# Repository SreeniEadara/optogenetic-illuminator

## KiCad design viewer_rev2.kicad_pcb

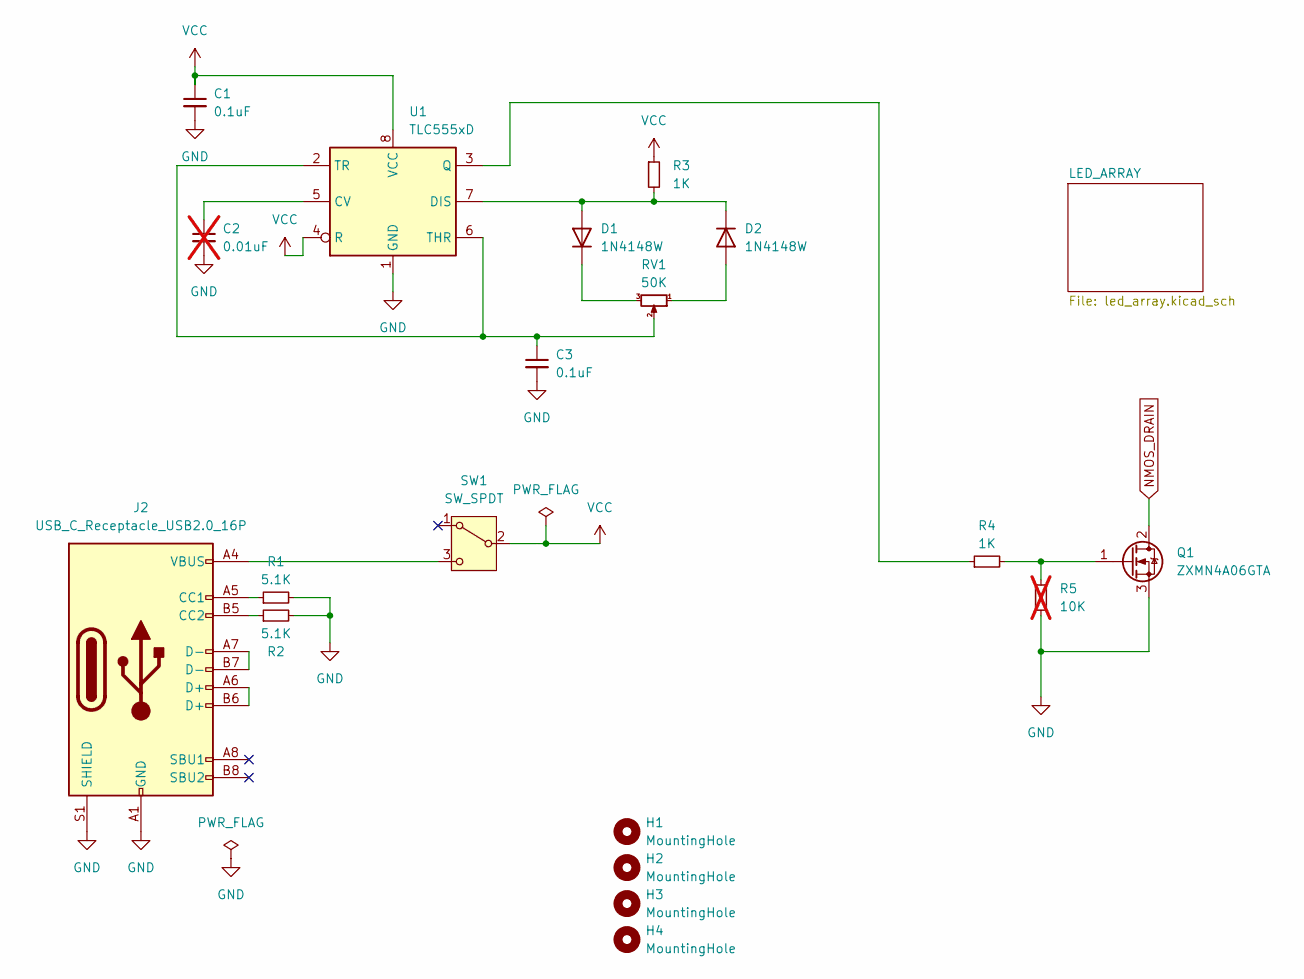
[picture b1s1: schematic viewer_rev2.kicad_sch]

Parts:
C1, C3: 0.1uF; C_0603_1608Metric; JLC C14663
C2: 0.01uF; C_0603_1608Metric; JLC C57112; not fitted
D1, D2: 1N4148W; D_SOD-123; DigiKey 1N4148W-E3-18CT-ND
H1, H2, H3, H4: MountingHole; MountingHole_3.2mm_M3_DIN965_Pad
J2: USB_C_Receptacle_USB2.0_16P; USB_C_Receptacle_GCT_USB4105-xx-A_16P_TopMnt_Horizontal; JLC C3039294
Q1: ZXMN4A06GTA; SOT-223-3_TabPin2; DigiKey ZXMN4A06GCT-ND
R1, R2: 5.1K; R_0603_1608Metric; JLC C23186
R3, R4: 1K; R_0603_1608Metric; JLC C21190
R5: 10K; R_0603_1608Metric; JLC C25804; not fitted
RV1: 50K; Potentiometer_Bourns_PTV09A-2_Single_Horizontal; DigiKey PTV09A-2020F-B503-ND
SW1: SW_SPDT; 1101MxSxAxx; DigiKey CKN11550-ND
U1: TLC555xD; SOIC-8_3.9x4.9mm_P1.27mm; DigiKey 296-1336-1-ND

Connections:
GND: C1.2, C2.2, C3.2, J2.A1 (GND), J2.A12 (GND), J2.B1 (GND), J2.B12 (GND), J2.S1 (SHIELD), Q1.3 (S), R1.2, R2.2, R5.2, U1.1 (GND)
NMOS_DRAIN: Q1.2 (D); also elsewhere on the board
unnamed: D1.2 (A), D2.1 (K), R3.2, U1.7 (DIS)
unnamed: D1.1 (K), RV1.3
unnamed: D2.2 (A), RV1.1
unnamed: J2.A5 (CC1), R1.1
unnamed: J2.B5 (CC2), R2.1
unnamed: J2.A6 (D+), J2.B6 (D+)
unnamed: J2.A7 (D-), J2.B7 (D-)
unnamed: Q1.1 (G), R4.2, R5.1
unnamed: J2.A4 (VBUS), J2.A9 (VBUS), J2.B4 (VBUS), J2.B9 (VBUS), SW1.3 (C)
unnamed: C2.1, U1.5 (CV)
unnamed: R4.1, U1.3 (Q)
unnamed: C3.1, RV1.2, U1.2 (TR), U1.6 (THR)
VCC: C1.1, R3.1, SW1.2 (B), U1.4 (R), U1.8 (VCC); also elsewhere on the board

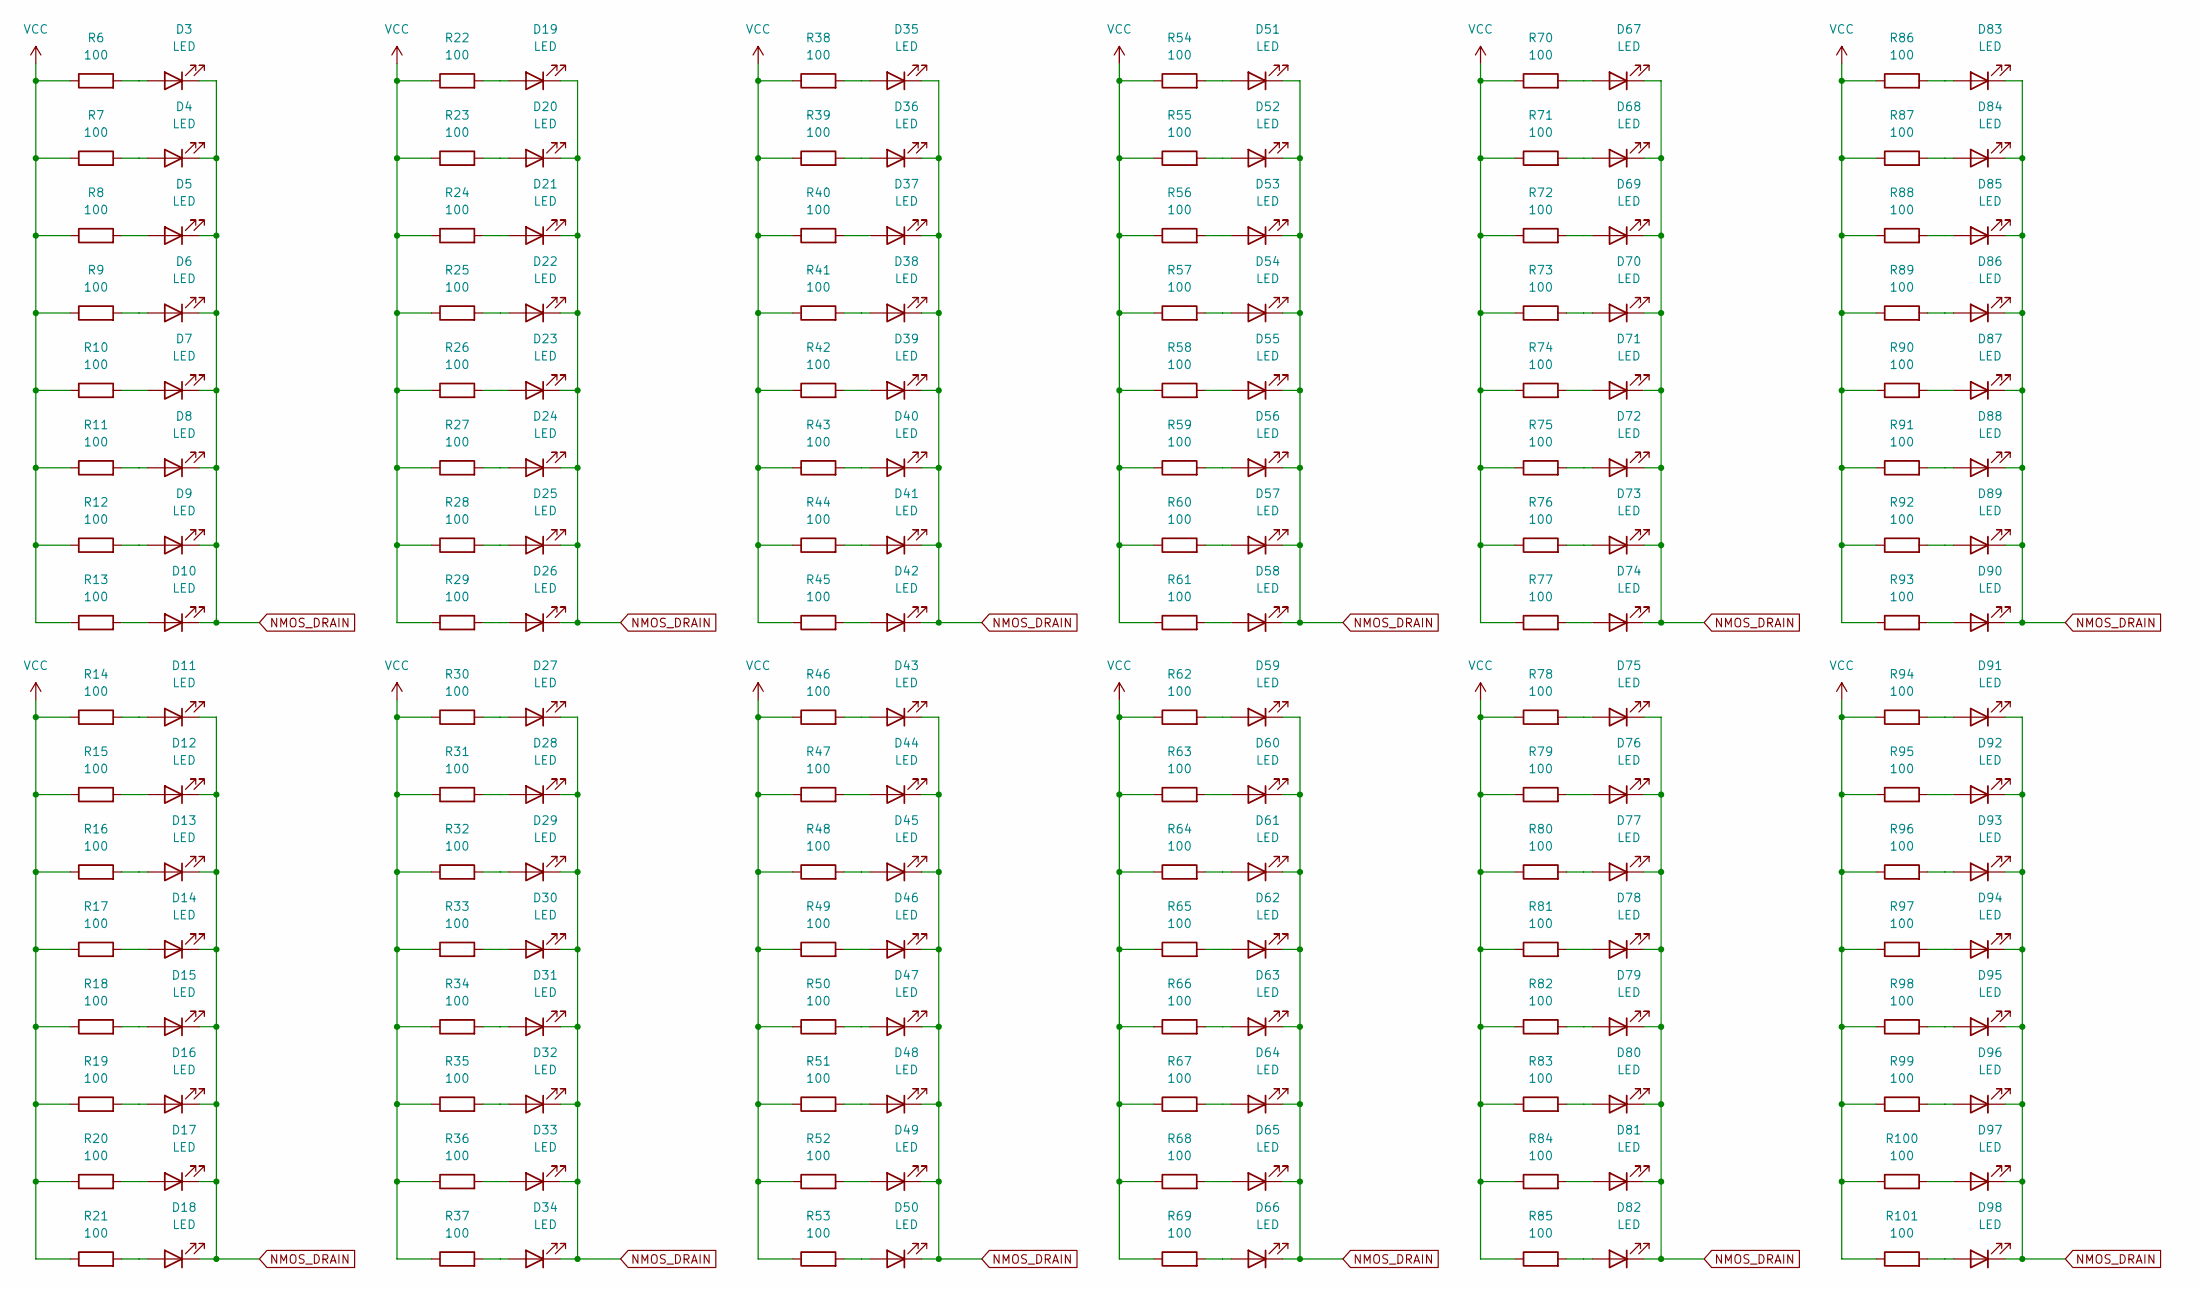
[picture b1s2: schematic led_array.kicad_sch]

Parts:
D3, D4, D5, D6, D7, D8, D9, D10, D11, D12, D13, D14, D15, D16, D17, D18, D19, D20, D21, D22, D23, D24, D25, D26, D27, D28, D29, D30, D31, D32, D33, D34, D35, D36, D37, D38, D39, D40, D41, D42, D43, D44, D45, D46, D47, D48, D49, D50, D51, D52, D53, D54, D55, D56, D57, D58, D59, D60, D61, D62, D63, D64, D65, D66, D67, D68, D69, D70, D71, D72, D73, D74, D75, D76, D77, D78, D79, D80, D81, D82, D83, D84, D85, D86, D87, D88, D89, D90, D91, D92, D93, D94, D95, D96, D97, D98: LED; LED_0603_1608Metric; DigiKey 754-1434-1-ND
R6, R7, R8, R9, R10, R11, R12, R13, R14, R15, R16, R17, R18, R19, R20, R21, R22, R23, R24, R25, R26, R27, R28, R29, R30, R31, R32, R33, R34, R35, R36, R37, R38, R39, R40, R41, R42, R43, R44, R45, R46, R47, R48, R49, R50, R51, R52, R53, R54, R55, R56, R57, R58, R59, R60, R61, R62, R63, R64, R65, R66, R67, R68, R69, R70, R71, R72, R73, R74, R75, R76, R77, R78, R79, R80, R81, R82, R83, R84, R85, R86, R87, R88, R89, R90, R91, R92, R93, R94, R95, R96, R97, R98, R99, R100, R101: 100; R_0603_1608Metric; JLC C22775

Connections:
NMOS_DRAIN: D3.1 (K), D4.1 (K), D5.1 (K), D6.1 (K), D7.1 (K), D8.1 (K), D9.1 (K), D10.1 (K), D11.1 (K), D12.1 (K), D13.1 (K), D14.1 (K), D15.1 (K), D16.1 (K), D17.1 (K), D18.1 (K), D19.1 (K), D20.1 (K), D21.1 (K), D22.1 (K), D23.1 (K), D24.1 (K), D25.1 (K), D26.1 (K), D27.1 (K), D28.1 (K), D29.1 (K), D30.1 (K), D31.1 (K), D32.1 (K), D33.1 (K), D34.1 (K), D35.1 (K), D36.1 (K), D37.1 (K), D38.1 (K), D39.1 (K), D40.1 (K), D41.1 (K), D42.1 (K), D43.1 (K), D44.1 (K), D45.1 (K), D46.1 (K), D47.1 (K), D48.1 (K), D49.1 (K), D50.1 (K), D51.1 (K), D52.1 (K), D53.1 (K), D54.1 (K), D55.1 (K), D56.1 (K), D57.1 (K), D58.1 (K), D59.1 (K), D60.1 (K), D61.1 (K), D62.1 (K), D63.1 (K), D64.1 (K), D65.1 (K), D66.1 (K), D67.1 (K), D68.1 (K), D69.1 (K), D70.1 (K), D71.1 (K), D72.1 (K), D73.1 (K), D74.1 (K), D75.1 (K), D76.1 (K), D77.1 (K), D78.1 (K), D79.1 (K), D80.1 (K), D81.1 (K), D82.1 (K), D83.1 (K), D84.1 (K), D85.1 (K), D86.1 (K), D87.1 (K), D88.1 (K), D89.1 (K), D90.1 (K), D91.1 (K), D92.1 (K), D93.1 (K), D94.1 (K), D95.1 (K), D96.1 (K), D97.1 (K), D98.1 (K); also elsewhere on the board
unnamed: D3.2 (A), R6.2
unnamed: D4.2 (A), R7.2
unnamed: D5.2 (A), R8.2
unnamed: D6.2 (A), R9.2
unnamed: D7.2 (A), R10.2
unnamed: D8.2 (A), R11.2
unnamed: D9.2 (A), R12.2
unnamed: D10.2 (A), R13.2
unnamed: D11.2 (A), R14.2
unnamed: D12.2 (A), R15.2
unnamed: D13.2 (A), R16.2
unnamed: D14.2 (A), R17.2
unnamed: D15.2 (A), R18.2
unnamed: D16.2 (A), R19.2
unnamed: D17.2 (A), R20.2
unnamed: D18.2 (A), R21.2
unnamed: D19.2 (A), R22.2
unnamed: D20.2 (A), R23.2
unnamed: D21.2 (A), R24.2
unnamed: D22.2 (A), R25.2
unnamed: D23.2 (A), R26.2
unnamed: D24.2 (A), R27.2
unnamed: D25.2 (A), R28.2
unnamed: D26.2 (A), R29.2
unnamed: D27.2 (A), R30.2
unnamed: D28.2 (A), R31.2
unnamed: D29.2 (A), R32.2
unnamed: D30.2 (A), R33.2
unnamed: D31.2 (A), R34.2
unnamed: D32.2 (A), R35.2
unnamed: D33.2 (A), R36.2
unnamed: D34.2 (A), R37.2
unnamed: D35.2 (A), R38.2
unnamed: D36.2 (A), R39.2
unnamed: D37.2 (A), R40.2
unnamed: D38.2 (A), R41.2
unnamed: D39.2 (A), R42.2
unnamed: D40.2 (A), R43.2
unnamed: D41.2 (A), R44.2
unnamed: D42.2 (A), R45.2
unnamed: D43.2 (A), R46.2
unnamed: D44.2 (A), R47.2
unnamed: D45.2 (A), R48.2
unnamed: D46.2 (A), R49.2
unnamed: D47.2 (A), R50.2
unnamed: D48.2 (A), R51.2
unnamed: D49.2 (A), R52.2
unnamed: D50.2 (A), R53.2
unnamed: D51.2 (A), R54.2
unnamed: D52.2 (A), R55.2
unnamed: D53.2 (A), R56.2
unnamed: D54.2 (A), R57.2
unnamed: D55.2 (A), R58.2
unnamed: D56.2 (A), R59.2
unnamed: D57.2 (A), R60.2
unnamed: D58.2 (A), R61.2
unnamed: D59.2 (A), R62.2
unnamed: D60.2 (A), R63.2
unnamed: D61.2 (A), R64.2
unnamed: D62.2 (A), R65.2
unnamed: D63.2 (A), R66.2
unnamed: D64.2 (A), R67.2
unnamed: D65.2 (A), R68.2
unnamed: D66.2 (A), R69.2
unnamed: D67.2 (A), R70.2
unnamed: D68.2 (A), R71.2
unnamed: D69.2 (A), R72.2
unnamed: D70.2 (A), R73.2
unnamed: D71.2 (A), R74.2
unnamed: D72.2 (A), R75.2
unnamed: D73.2 (A), R76.2
unnamed: D74.2 (A), R77.2
unnamed: D75.2 (A), R78.2
unnamed: D76.2 (A), R79.2
unnamed: D77.2 (A), R80.2
unnamed: D78.2 (A), R81.2
unnamed: D79.2 (A), R82.2
unnamed: D80.2 (A), R83.2
unnamed: D81.2 (A), R84.2
unnamed: D82.2 (A), R85.2
unnamed: D83.2 (A), R86.2
unnamed: D84.2 (A), R87.2
unnamed: D85.2 (A), R88.2
unnamed: D86.2 (A), R89.2
unnamed: D87.2 (A), R90.2
unnamed: D88.2 (A), R91.2
unnamed: D89.2 (A), R92.2
unnamed: D90.2 (A), R93.2
unnamed: D91.2 (A), R94.2
unnamed: D92.2 (A), R95.2
unnamed: D93.2 (A), R96.2
unnamed: D94.2 (A), R97.2
unnamed: D95.2 (A), R98.2
unnamed: D96.2 (A), R99.2
unnamed: D97.2 (A), R100.2
unnamed: D98.2 (A), R101.2
VCC: R6.1, R7.1, R8.1, R9.1, R10.1, R11.1, R12.1, R13.1, R14.1, R15.1, R16.1, R17.1, R18.1, R19.1, R20.1, R21.1, R22.1, R23.1, R24.1, R25.1, R26.1, R27.1, R28.1, R29.1, R30.1, R31.1, R32.1, R33.1, R34.1, R35.1, R36.1, R37.1, R38.1, R39.1, R40.1, R41.1, R42.1, R43.1, R44.1, R45.1, R46.1, R47.1, R48.1, R49.1, R50.1, R51.1, R52.1, R53.1, R54.1, R55.1, R56.1, R57.1, R58.1, R59.1, R60.1, R61.1, R62.1, R63.1, R64.1, R65.1, R66.1, R67.1, R68.1, R69.1, R70.1, R71.1, R72.1, R73.1, R74.1, R75.1, R76.1, R77.1, R78.1, R79.1, R80.1, R81.1, R82.1, R83.1, R84.1, R85.1, R86.1, R87.1, R88.1, R89.1, R90.1, R91.1, R92.1, R93.1, R94.1, R95.1, R96.1, R97.1, R98.1, R99.1, R100.1, R101.1; also elsewhere on the board

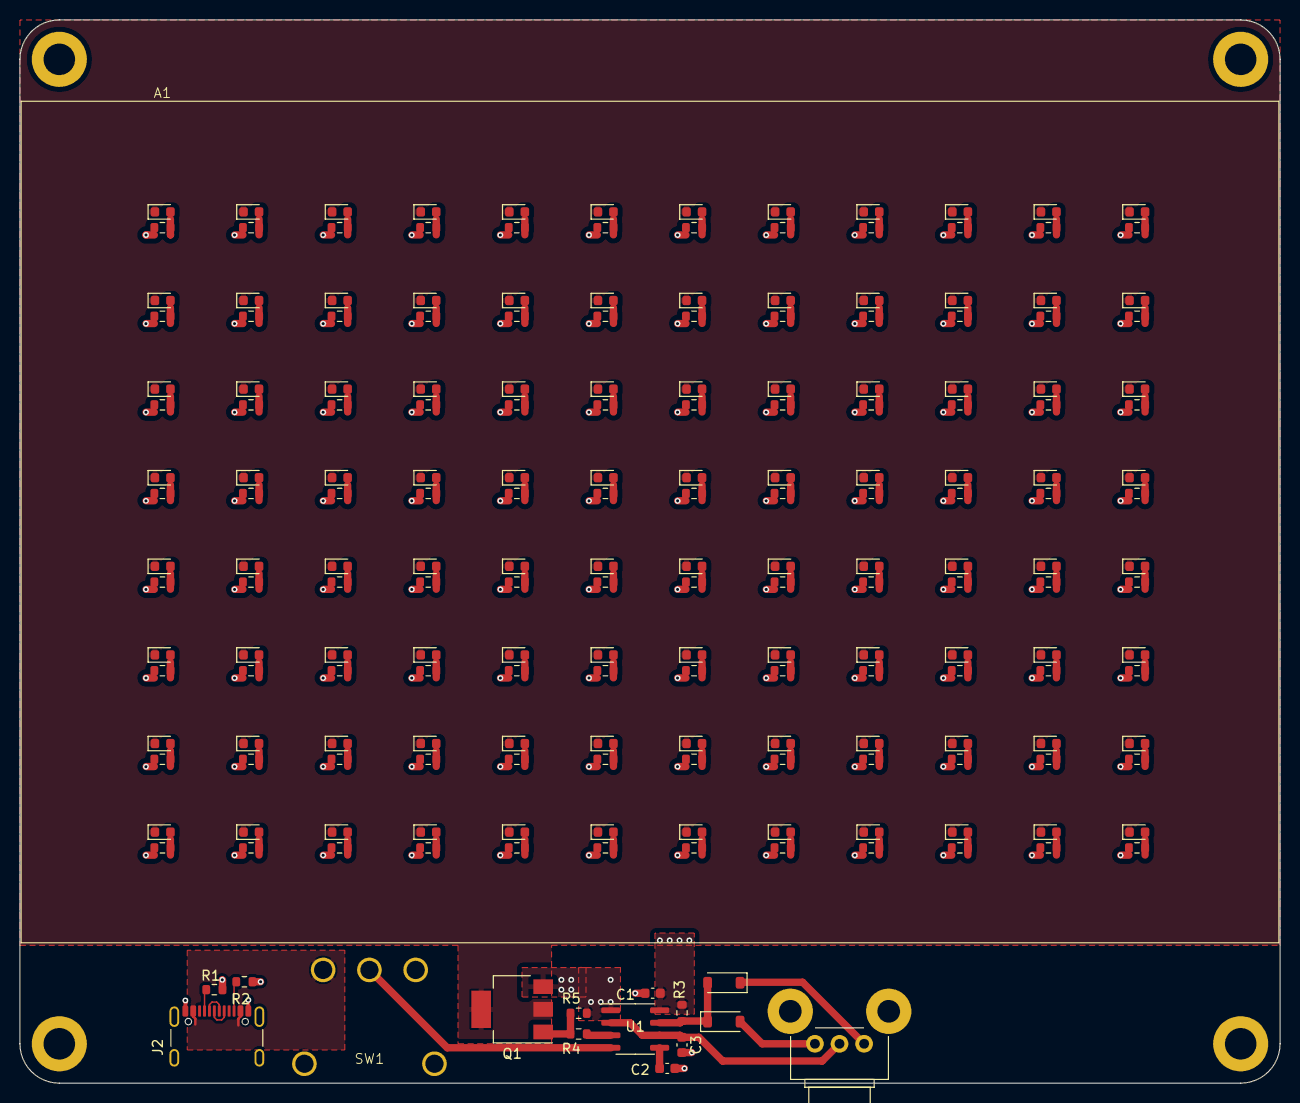
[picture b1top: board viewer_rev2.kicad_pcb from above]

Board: 2 copper layers, 128.0 x 108.0 mm, 211 parts (0 on the bottom side), 111 nets.

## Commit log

2024-06-06 drafted optogenetic illuminator
2024-06-07 Draft version for 96 well plate
2024-06-08 update USB-C conn and add JLC PNs
2024-06-08 fix gitignore
2024-06-08 Modify clearance setting and change to fit. Other changes to satisfy ERC / DRC
2024-06-08 update manufacturing outputs following changes of last commit
2024-06-08 Add DigiKey and Mouser PNs. Update manf outputs
2024-06-08 part change to higher current switch. Export manf for new PCB and new BOM.
